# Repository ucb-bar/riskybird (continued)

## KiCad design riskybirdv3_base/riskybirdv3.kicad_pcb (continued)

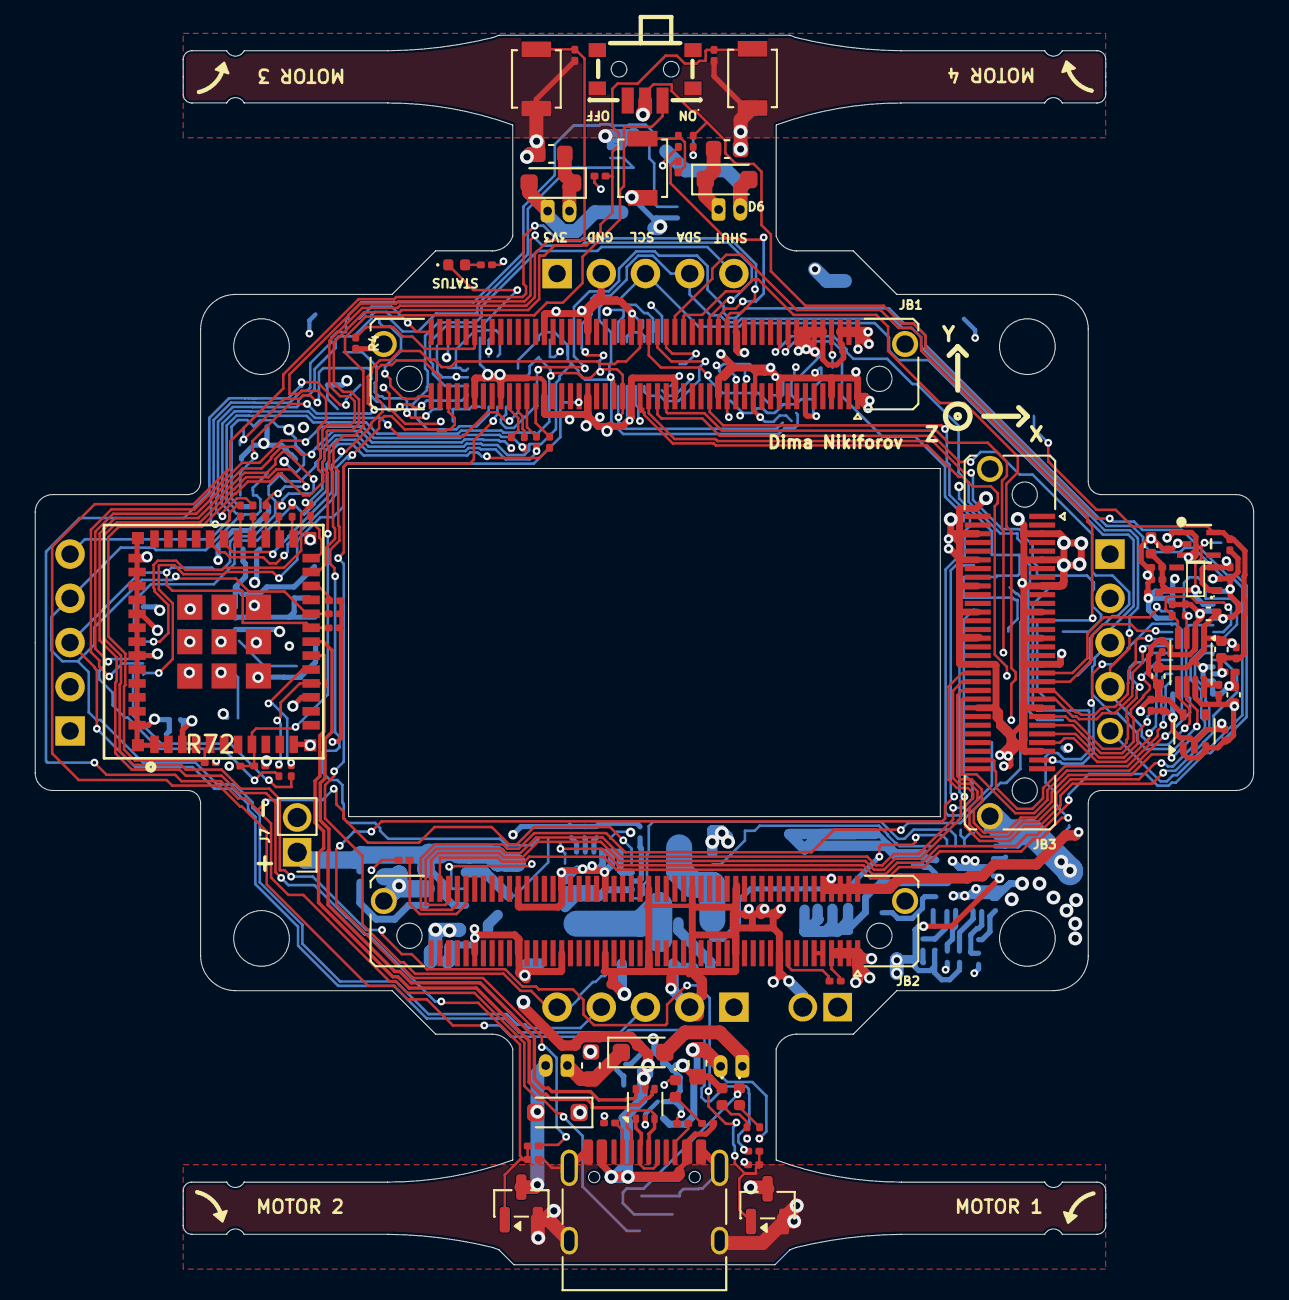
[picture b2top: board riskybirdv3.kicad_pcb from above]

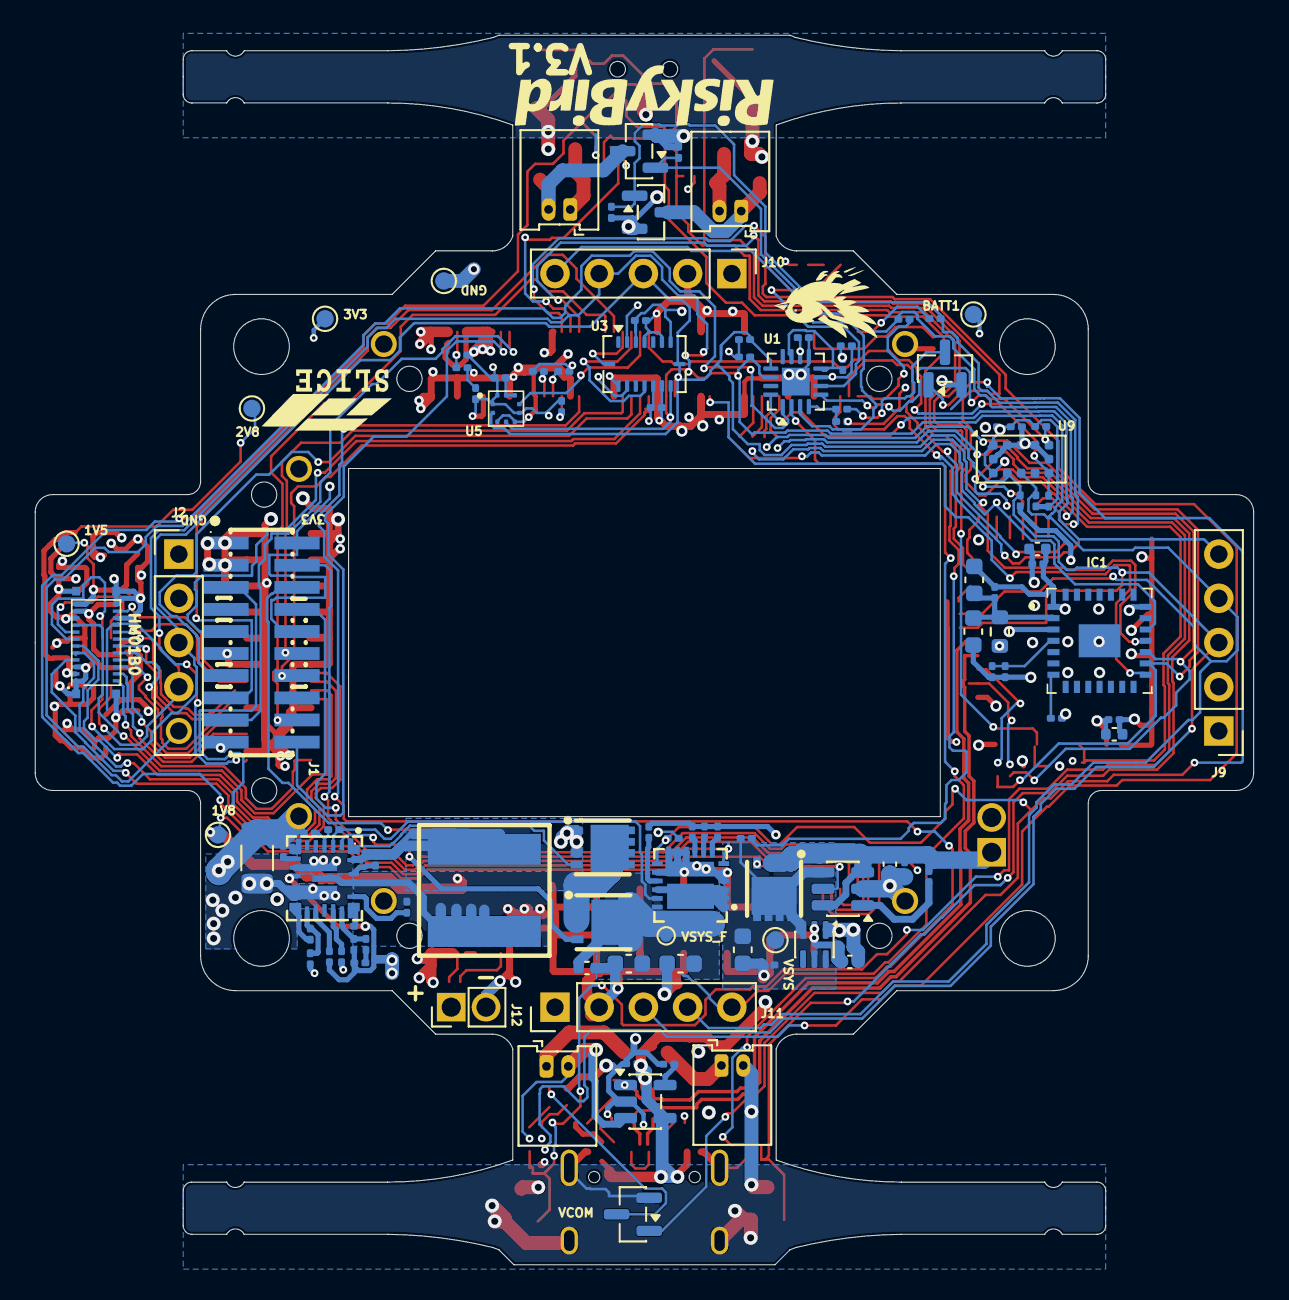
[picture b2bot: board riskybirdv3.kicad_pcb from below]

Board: 4 copper layers, 70.0 x 70.6 mm, 199 parts (108 on the bottom side), 138 nets.

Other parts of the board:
G1: LOGO

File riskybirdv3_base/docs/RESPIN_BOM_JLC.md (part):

# RESPIN — JLCPCB Assembly BOM audit + substitution list

**Project:** riskybird v3 base board (`riskybirdv3_base/riskybirdv3.kicad_sch`)
**Goal:** a BOM JLC can use to **directly SMT-assemble** the respin board — every part verified against JLC's *assembly parts library* (Basic / Preferred Extended / Extended), not merely "listed on LCSC."
**Status:** Audit only — **no `.kicad_*` edits, nothing committed.** Companion to `RESPIN_POWER_RAIL.md`, `RESPIN_POWER_U2.md`, `RESPIN_POWER_BROWNOUT.md`, `RESPIN_CHECKLIST.md`, `OFF-BOM_PARTS_ORDER.md`.
**Date:** 2026-08-16

---

## 0. Method, data source, reliability

- **BOM extracted** from the live schematic with `kicad-cli sch export bom` (grouped by Value+Footprint). The schematic carries LCSC C-numbers in a property named **`LCSC Part`** (126 of 419 symbols populated) — the bennymeg *Fabrication Toolkit* plugin (this project's `fabrication-toolkit-options.json`) reads that field, so the flow is compatible. There is **no** bare `LCSC` property; parts without a `LCSC Part` value are the "no-LCSC" gaps below.
- **JLC assembly status** (in-catalog? class? stock? price?) queried from **`jlcsearch.tscircuit.com/api`**, which is a hosted mirror of the **community `jlcparts` SQLite database** (github.com/yaqwsx/jlcparts) — i.e. JLC's *assembly* catalog, exactly the source the brief recommended. The GitHub-Pages raw DB path (`yaqwsx.github.io/jlcparts/data/cache.json`) now 404s, so the tscircuit mirror was used instead. Fields returned per part: `is_basic`, `is_preferred`, `stock`, `price`, `package`, `mfr`, `description`.
- **Reliability:**
  - **In-catalog (assemblable y/n) — HIGH.** A part returned by the mirror is in the jlcparts assembly DB; a part with **0 results is not in the assembly catalog** (may be LCSC-order-only or discontinued). This is how the BMP390 and the eFuse gaps were found.
  - **Class (Basic/Preferred/Extended) — HIGH.** Stable field.
  - **Stock — MEDIUM (point-in-time snapshot; some noise).** The jlcparts DB is refreshed periodically, so absolute stock is approximate. Observed noise: one jellybean 4.7 kΩ 0201 briefly read "9" then "1.3 M" on re-query. **Treat all stock counts below as order-time-verify**, especially the low ones. Re-check any part at `jlcpcb.com/partdetail/<C#>` before the order.
  - **Not verifiable from this source:** exact assembly-line placement rules for odd packages, and JLC's per-order "economic vs standard" surcharge for Extended parts (every non-Basic part on an SMT order incurs a per-unique-part feeder fee — noted where it matters).

**Headline:** The board is **NOT yet fully JLC-assemblable as drawn.** The silicon is nearly all in the catalog, but **~26 line-items have no `LCSC Part` field** (JLC would skip them), **1 part is genuinely not in the assembly catalog (U5 BMP390)**, and the **3 new power-rail parts** need their C-numbers pinned (buck-boost OK, eFuse + inductor need the corrected C#s below). All gaps have a concrete JLC-assemblable fix listed. Count: **1 not-assemblable, ~26 no-LCSC-field, ~6 low-stock watch items.**

## 0a. Applied changes (2026-08-16) — U5 swap + IC1 DNP/LCSC

Two fixes were **applied to `riskybirdv3.kicad_sch` AND `riskybirdv3.kicad_pcb`** (backups `*.bak_20260816_142627`; **not committed**; validated: BOM re-export ✓, ERC unchanged at 182 before/after, PCB loads via pcbnew, IC1 now present in the `--exclude-dnp` position file):

- **U5 BMP390 → BMP388** (the not-assemblable part). Value `BMP390→BMP388`, MPN `BMP390L→BMP388`, `LCSC Part C2684802→C779278`, in both schematic instance and PCB footprint fields. **Footprint land pattern `riskybird:BMP390` kept** (BMP388 = same LGA-10 2×2 package/pinout). *Note:* the `lib_id`/footprint name still reads "BMP390" (cosmetic; the BOM Value/MPN/LCSC are now BMP388/C779278). Firmware baro driver must cover BMP388.
- **IC1 PMW3901 un-DNP'd + LCSC added.** Cleared `(attr smd dnp)` → `(attr smd)` on the PCB footprint (the actual "BOM-yes/CPL-no" desync cause — the schematic symbol was already `dnp=no`), and added `LCSC Part = C43496881` to both the schematic symbol and PCB footprint. IC1 now exports into the position/CPL file.

**Still a GUI follow-up (recommended):** open KiCAD and run **Update PCB from Schematic (F8)** once to confirm sch↔pcb parity (fields were edited on both sides to match, so no geometry change is expected). And when the *other* §2 no-LCSC parts get their C#s, pin them in the schematic and re-run F8.

**B2B connectors actually ordered (from the real order BOM `production/riskybirdv3-bom.csv`, 2026-07-26):** the **LSHM-04.0 / 8.00 mm stack** — JB1+JB2 = `LSHM-150-04.0-L-DV-A-S-K-TR` (**C5367357**, qty 2), JB3 = `LSHM-130-04.0-L-DV-A-S-K-TR` (**C3645597**, qty 1). **Not** the 03.0/7.00 mm option. So the current schematic already matches what was ordered; the 03.0-vs-04.0 "contradiction" resolves to **04.0** for the respin (and 04.0 has more JB1/JB2 stock than 03.0 — 11 vs 1).

---

## 1. Full BOM — JLC assembly status

Legend for **STATUS**: **OK** = has C#, in catalog, adequate stock · **NO-LCSC** = in catalog but no `LCSC Part` field in schematic (JLC will skip until assigned) · **NOT-ASM** = not in JLC assembly catalog · **LOW-STK** = assemblable but thin stock (order-time verify) · **THT** = through-hole (JLC THT-assembly upcharge, else hand-solder) · **N/A** = not a placed part.

Class = Basic / Pref (Preferred Extended) / Ext (Extended). Stock/price are the 2026-08-16 snapshot.

| Ref(s) | Value | Footprint | MPN | LCSC (in sch) | Class | Stock | Price | STATUS |
|---|---|---|---|---|---|---|---|---|
| 1V5,1V8,2V8,3V3,BATT1,TP1,TP2 | TestPoint | Pad_D1.0mm | — | — | — | — | — | **N/A** (bare pads, not placed) |
| C1 | 4.7µ | 0201 | GRM035R60J475ME15D | C335103 | Ext | 684k | $0.20 | OK |
| C2,C3,C40,C41 | 47µF | 0603 | — | — | — | — | — | **NO-LCSC** → C140782 |
| C4,C5,C6,C7,C10,C13,C15,C38 | 100nF | 0201 | GRM033R60J104KE19D | C76928 | Ext | 2.56M | $0.001 | OK |
| C8,C42,C59,C66 | 1µF | 0201 | CL03A105MQ3CSNH | C53067 | Ext | 43k | $0.004 | OK |
| C9,C39 | 4.7µF | 0201 | GRM035R60J475ME15D | C335103 | Ext | 684k | $0.20 | OK |
| C11,C12 | 22µF | 0603 | — | — | — | — | — | **NO-LCSC** → C59461 (Basic) |
| C14 | 10µF | 0402 | — | — | — | — | — | **NO-LCSC** → C15525 (Basic) |
| C16,C17 | 100n | 0201 | GRM033R60J104KE19D | C76928 | Ext | 2.56M | $0.001 | OK |
| C37,C43,C44,C45,C50,C51,C54,C56–C58,C60,C61,C77 | 0.1µ | 0201 | GRM033R60J104KE19D | C76928 | Ext | 2.56M | $0.001 | OK |
| C46,C47,C48,C49,C62,C67,C73,C74,C75 | 10µ | 0402 | — | — | — | — | — | **NO-LCSC** → C15525 (Basic) |
| C52,C53,C55,C68,C69,C70 | 1µ | 0201 | CL03A105MQ3CSNH | C53067 | Ext | 43k | $0.004 | OK |
| C63 | 150µ | 1206 | — | — | — | — | — | **NO-LCSC** → C528968 |
| C64 | 470p | 0201 | GRM033R71H471KA12D | C161493 | Ext | 12k | $0.003 | OK |
| C65 | 4.7µ | 0402 | — | — | — | — | — | **NO-LCSC** → C23733 (Basic) |
| C71,C72 | 0.1µ | 0402 | — | — | — | — | — | **NO-LCSC** → C1525 (Basic) |
| D1,D4 | LED | 0402 | — | — | — | — | — | **NO-LCSC** → C965793 (grn) / C20613596 (wht) — pick color |
| D2,D3,D5,D6 | BAT54JFILM | SOD-323 | — | — | — | — | — | **NO-LCSC** → C86299 |
| D7 | LED_RED | 0402 | — | — | — | — | — | **NO-LCSC** → C25503345 |
| HM01B0 | camera recept. | 5055502420 | 505550-2420 | C3642262 | Ext | 5112 | $0.37 | OK (mates HM01B0 module plug) |
| IC1 | PMW3901MB-TXQT | COB/LGA-28 | — | **C43496881** ✅ | Ext | 596 | $4.96 | **FIXED 2026-08-16** — LCSC added + PCB `dnp` cleared (§0a) |
| J1 | FTSH-110-01-L-DV-K-TR | 2×10 1.27mm | FTSH-110-01-L-DV-K-TR | C20728453 | Ext | **31** | $2.85 | **LOW-STK** (debug hdr) |
| J2,J9,J10,J11 | Conn_01x05 | 1×5 2.54mm hdr | — | — | Ext | 251k | $0.03 | **NO-LCSC + THT** → C492404 |
| J3,J4,J5,J6 | Conn_01x02 | Molex PicoBlade 53048-0210 | 53048-0210 | C505099 | Ext | 30.8k | $0.14 | OK as drawn — **respin: upsize** (1A/contact, see §5) |
| J8 | USB-C recept. | TYPE-C-31-M-12 | TYPE-C-31-M-12 | C165948 | Ext | 336k | $0.16 | OK |
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
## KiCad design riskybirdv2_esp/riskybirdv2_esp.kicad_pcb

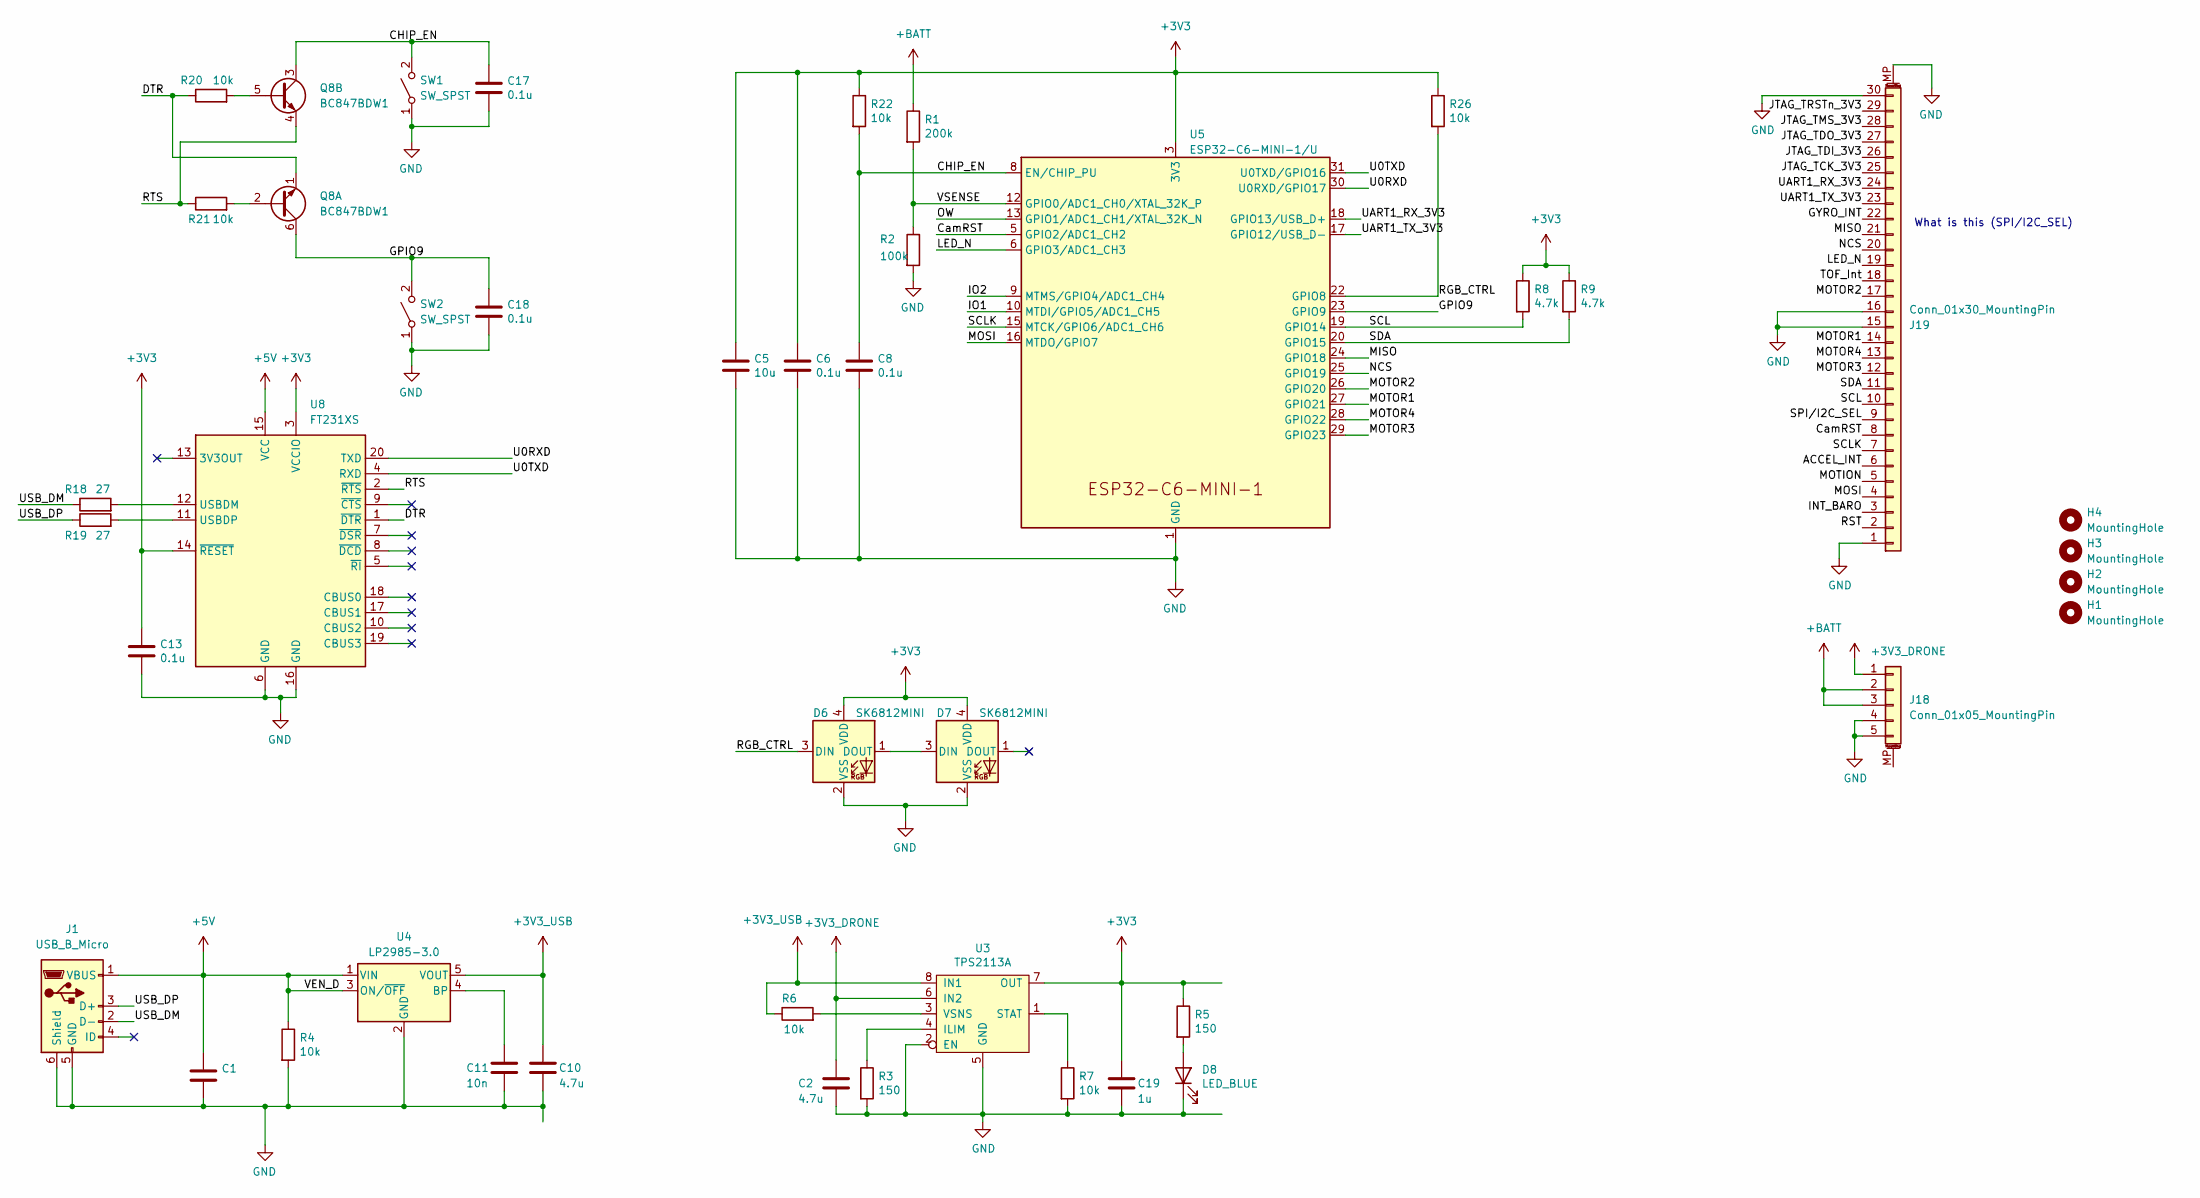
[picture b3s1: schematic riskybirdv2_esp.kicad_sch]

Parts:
C1, C2, C10: 4.7u; C_0402_1005Metric
C5: 10u; C_0402_1005Metric
C6, C8, C13, C17, C18: 0.1u; C_0402_1005Metric
C11: 10n; C_0402_1005Metric
C19: 1u; C_0402_1005Metric
D6, D7: SK6812MINI; LED_SK6812MINI_PLCC4_3.5x3.5mm_P1.75mm
D8: LED_BLUE; LED_0805_2012Metric_Pad1.15x1.40mm_HandSolder
H1, H2, H3, H4: MountingHole; MountingHole_2.2mm_M2
J1: USB_B_Micro; USB_Micro-B_Molex_47346-0001
J18: Conn_01x05_MountingPin; JST_ZH_B5B-ZR_1x05_P1.50mm_Vertical
J19: Conn_01x30_MountingPin; Hirose_FH12-30S-0.5SH_1x30-1MP_P0.50mm_Horizontal
Q8: BC847BDW1; SOT-363_SC-70-6
R1: 200k; R_0402_1005Metric
R2: 100k; R_0402_1005Metric
R3, R5: 150; R_0402_1005Metric
R4, R6, R7, R20, R21, R22, R26: 10k; R_0402_1005Metric
R8, R9: 4.7k; R_0402_1005Metric
R18, R19: 27; R_0402_1005Metric
SW1, SW2: SW_SPST; SW_SPST_B3U-1000P
U3: TPS2113A; TSSOP-8_4.4x3mm_P0.65mm
U4: LP2985-3.0; SOT-23-5
U5: ESP32-C6-MINI-1/U; ESP32-C6-MINI-1
U8: FT231XS; SSOP-20_3.9x8.7mm_P0.635mm

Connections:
+3V3: C5.1, C6.1, C13.1, C19.1, D6.4 (VDD), D7.4 (VDD), R5.1, R8.1, R9.1, R22.1, R26.1, U3.7 (OUT), U5.3 (3V3), U8.3 (VCCIO), U8.14 (~RESET)
+3V3_DRONE: C2.1, J18.1, U3.6 (IN2)
+3V3_USB: C10.1, R6.1, U3.8 (IN1), U4.5 (VOUT)
+5V: C1.1, J1.1 (VBUS), R4.1, U4.1 (VIN), U4.3 (ON/~OFF), U8.15 (VCC)
+BATT: J18.2, J18.3, R1.1
/ACCEL_INT: J19.6
/CHIP_EN: C8.1, C17.1, Q8.3 (C2), R22.2, SW1.2 (B), U5.8 (EN/CHIP_PU)
/CamRST: J19.8, U5.5 (GPIO2/ADC1_CH2)
/DTR: Q8.1 (E1), R20.1, U8.1 (~DTR)
/GPIO9: C18.1, Q8.6 (C1), SW2.2 (B), U5.23 (GPIO9)
/GYRO_INT: J19.22
/INT_BARO: J19.3
/IO1: U5.10 (MTDI/GPIO5/ADC1_CH5)
/IO2: U5.9 (MTMS/GPIO4/ADC1_CH4)
/JTAG_TCK_3V3: J19.25
/JTAG_TDI_3V3: J19.26
/JTAG_TDO_3V3: J19.27
/JTAG_TMS_3V3: J19.28
/JTAG_TRSTn_3V3: J19.29
/LED_N: J19.19, U5.6 (GPIO3/ADC1_CH3)
/MISO: J19.21, U5.24 (GPIO18)
/MOSI: J19.4, U5.16 (MTDO/GPIO7)
/MOTION: J19.5
/MOTOR1: J19.14, U5.27 (GPIO21)
/MOTOR2: J19.17, U5.26 (GPIO20)
/MOTOR3: J19.12, U5.29 (GPIO23)
/MOTOR4: J19.13, U5.28 (GPIO22)
/NCS: J19.20, U5.25 (GPIO19)
/OW: U5.13 (GPIO1/ADC1_CH1/XTAL_32K_N)
/RGB_CTRL: D6.3 (DIN), R26.2, U5.22 (GPIO8)
/RST: J19.2
/RTS: Q8.4 (E2), R21.1, U8.2 (~RTS)
/SCL: J19.10, R8.2, U5.19 (GPIO14)
/SCLK: J19.7, U5.15 (MTCK/GPIO6/ADC1_CH6)
/SDA: J19.11, R9.2, U5.20 (GPIO15)
/SPI/I2C_SEL: J19.9
/TOF_Int: J19.18
/U0RXD: U5.30 (U0RXD/GPIO17), U8.20 (TXD)
/U0TXD: U5.31 (U0TXD/GPIO16), U8.4 (RXD)
/UART1_RX_3V3: J19.24, U5.18 (GPIO13/USB_D+)
/UART1_TX_3V3: J19.23, U5.17 (GPIO12/USB_D-)
/USB_DM: J1.2 (D-), R18.1
/USB_DP: J1.3 (D+), R19.1
/VSENSE: R1.2, R2.1, U5.12 (GPIO0/ADC1_CH0/XTAL_32K_P)
GND: C1.2, C2.2, C5.2, C6.2, C8.2, C10.2, C11.2, C13.2, C17.2, C18.2, C19.2, D6.2 (VSS), D7.2 (VSS), D8.1 (K), J1.5 (GND), J1.6 (Shield), J18.4, J18.5, J19.1, J19.15, J19.16, J19.30, J19.MP (MountPin), R2.2, R3.2, R4.2, R7.2, SW1.1 (A), SW2.1 (A), U3.2 (EN), U3.5 (GND), U4.2 (GND), U5.1 (GND), U5.2 (GND), U5.11 (GND), U5.14 (GND), U5.36 (GND), U5.37 (GND), U5.38 (GND), U5.39 (GND), U5.40 (GND), U5.41 (GND), U5.42 (GND), U5.43 (GND), U5.44 (GND), U5.45 (GND), U5.46 (GND), U5.47 (GND), U5.48 (GND), U5.49 (GND), U5.50 (GND), U5.51 (GND), U5.52 (GND), U5.53 (GND), U8.6 (GND), U8.16 (GND)
unnamed: D6.1 (DOUT), D7.3 (DIN)
unnamed: D8.2 (A), R5.2
unnamed: Q8.2 (B1), R21.2
unnamed: Q8.5 (B2), R20.2
unnamed: R3.1, U3.4 (ILIM)
unnamed: R7.1, U3.1 (STAT)
unnamed: R6.2, U3.3 (VSNS)
unnamed: C11.1, U4.4 (BP)
unnamed: R18.2, U8.12 (USBDM)
unnamed: R19.2, U8.11 (USBDP)

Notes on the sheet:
What is this (SPI/I2C_SEL)

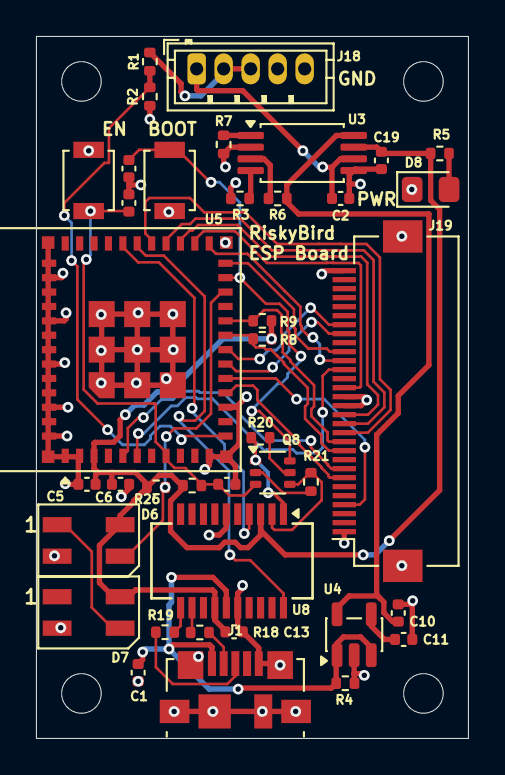
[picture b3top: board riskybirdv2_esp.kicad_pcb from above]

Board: 2 copper layers, 24.0 x 39.0 mm, 47 parts (0 on the bottom side), 40 nets.

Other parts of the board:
H1#2, H2#2, H3#2, H4#2: MountingHole; MountingHole_2.2mm_M2

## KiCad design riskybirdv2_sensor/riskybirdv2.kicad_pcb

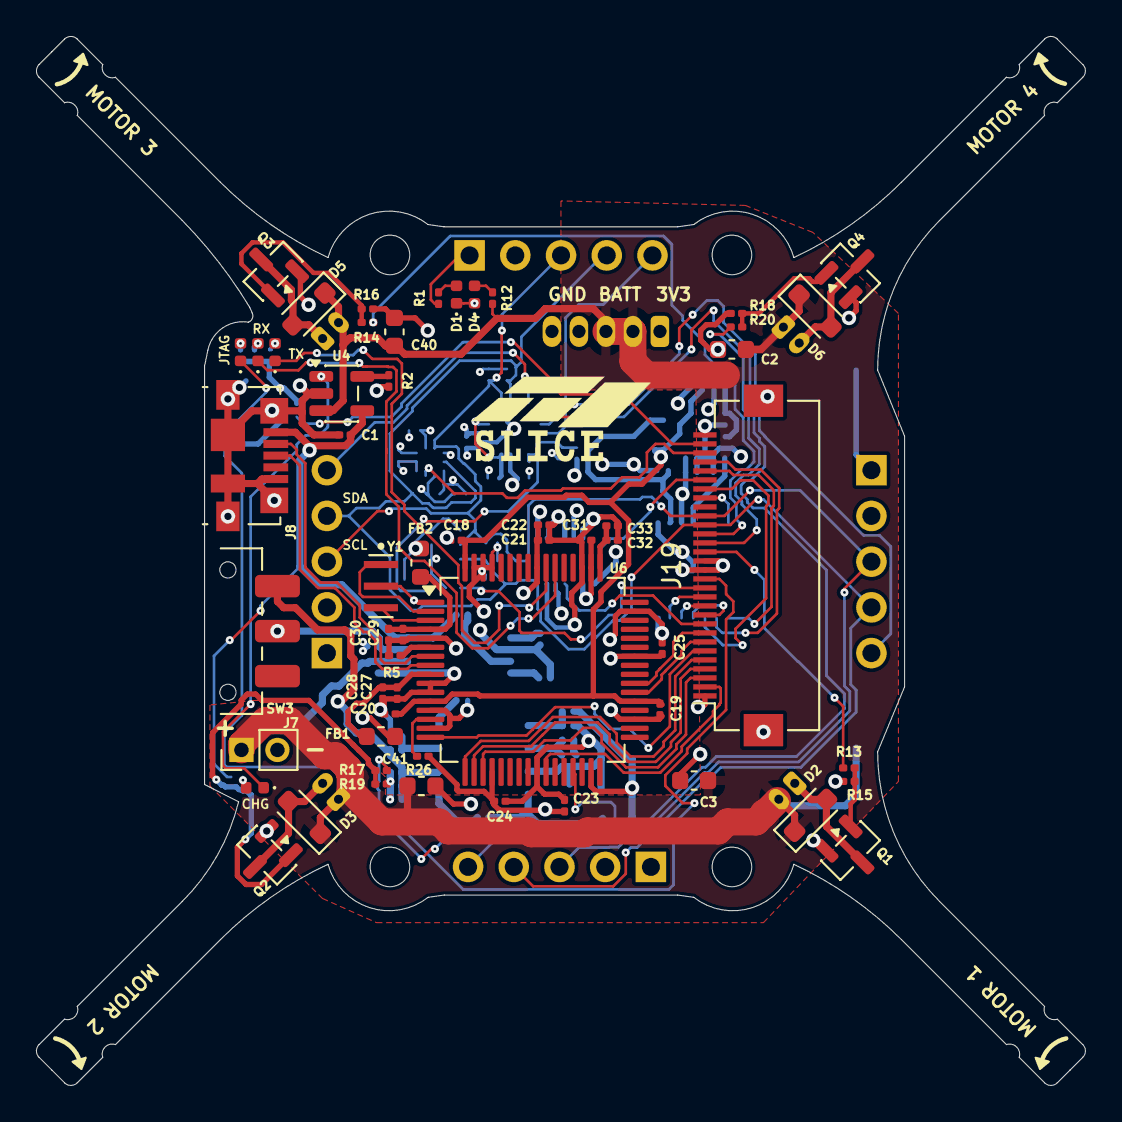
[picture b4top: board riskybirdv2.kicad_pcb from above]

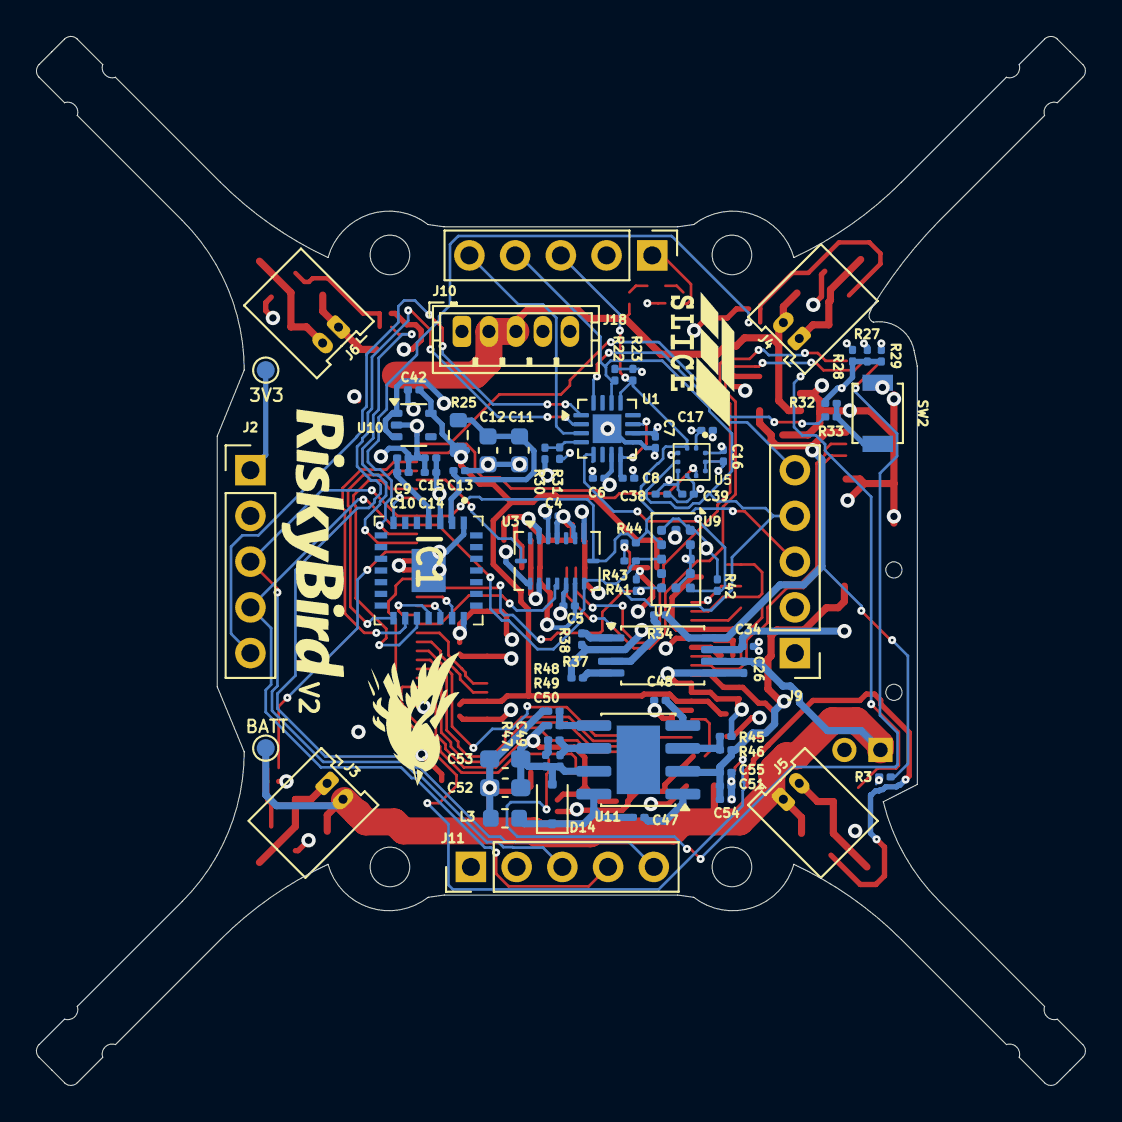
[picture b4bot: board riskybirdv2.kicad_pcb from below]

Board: 4 copper layers, 58.3 x 58.3 mm, 134 parts (73 on the bottom side), 80 nets.

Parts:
C1, C26: 4.7u; C_0201_0603Metric
C2, C3, C40, C41: 47uF; C_0603_1608Metric
C4, C5, C6, C7, C10, C13, C15, C18, C19, C20, C21, C22, C24, C25, C27, C29, C31, C33, C38: 100nF; C_0201_0603Metric
C8, C42: 1uF; C_0201_0603Metric
C9, C28, C30, C39, C51, C55: 4.7uF; C_0201_0603Metric
C11, C12: 22uF; C_0603_1608Metric
C14, C23: 10uF; C_0201_0603Metric
C16, C17: 100n; C_0201_0603Metric
C32: 3.3uF; C_0201_0603Metric
C34: 1u; C_0201_0603Metric
C47: 0.1uF; C_0201_0603Metric
C48, C54: 0.01uF; C_0201_0603Metric
C49: 1000pF; C_0201_0603Metric
C50: 47pF; C_0201_0603Metric
C52, C53: 47uF; C_0603_1608Metric_Pad1.08x0.95mm_HandSolder
D1, D4, D10, D11, D12: LED; LED_0402_1005Metric
D2, D3, D5, D6: BAT54JFILM; D_SOD-323_HandSoldering
D7: LED_RED; LED_0402_1005Metric
D14: BAT54J; D_SOD-323F
FB1, FB2: 600R@100MHz/0.5A; L_0603_1608Metric
FID1: DroneFrame; riskybird_frame
H1, H2, H3, H4: MountingHole; MountingHole_2.2mm_M2
IC1: PMW3901MB-TXQT; PMW3901MBTXQT
J2, J9, J10, J11: Conn_01x05; PinHeader_1x05_P2.54mm_Vertical
J3, J4, J5, J6: Conn_01x02; Molex_PicoBlade_53048-0210_1x02_P1.25mm_Horizontal
J7: Conn_01x02; PinHeader_1x02_P2.00mm_Vertical
J8: USB_B_Micro; USB_Micro-B_Molex_47346-0001
J18: Conn_01x05_MountingPin; JST_ZH_B5B-ZR_1x05_P1.50mm_Vertical
J19: Conn_01x30_MountingPin; Hirose_FH12-30S-0.5SH_1x30-1MP_P0.50mm_Horizontal
L3: 6.8uH; L_0603_1608Metric
Q1, Q2, Q3, Q4: SI2302; SOT-23
R1, R3, R12, R27, R28, R29, R37: 150; R_0201_0603Metric
R2: 2k; R_0201_0603Metric
R5: 12k; R_0201_0603Metric
R13, R14, R17, R18: 47R; R_0201_0603Metric
R15, R16, R19, R20, R34, R38, R41, R42: 10k; R_0201_0603Metric
R22, R23, R43, R44: 4.7K; R_0201_0603Metric
R25: 3; R_0603_1608Metric
R26: 1k; R_0201_0603Metric
R30: 200K; R_0201_0603Metric
R31: 100K; R_0201_0603Metric
R32: 10K; R_0201_0603Metric
R33: 100; R_0201_0603Metric
R45: 68.1k; R_0201_0603Metric
R46: 332k; R_0201_0603Metric
R47: 29.4k; R_0201_0603Metric
R48: 10.2k; R_0201_0603Metric
R49: 3.24k; R_0201_0603Metric
SW2: SW_SPST; SW_SPST_B3U-1000P
SW3: SW_SPST; SW_SPDT_CK_JS102011SAQN
TP1, TP6: TestPoint; TestPoint_Pad_D1.0mm
U1: ADS7128IRTER; WQFN-16-1EP_3x3mm_P0.5mm_EP1.6x1.6mm
U3: BMI088; Bosch_LGA-16_4.5x3mm_P0.5mm_LayoutBorder7x1y_ClockwisePinNu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
U4: MCP73831-2-OT; SOT-23-5
U5: BMP390
U6: FT2232HL-REEL; LQFP-64_10x10mm_P0.5mm
U7: TPS2113A; TSSOP-8_4.4x3mm_P0.65mm
U9: VL53L1CXV0FY1; ST_VL53L1x
U10: TLV70018DCKR; SOT-353_SC-70-5
U11: TPS54331D; SOIC-8-1EP_3.9x4.9mm_P1.27mm_EP2.41x3.81mm
Y1: f; OSC_CSTNE12M0G550000R0

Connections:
+1V8: C18.1, C19.1, C20.1, C42.1, R25.2, U6.12 (VCORE), U6.37 (VCORE), U6.64 (VCORE), U10.5 (OUT)
+3V3: C4.1, C5.1, C6.1, C7.1, C14.1, C15.1, C16.1, C17.1, C21.1, C22.1, C23.1, C24.1, C25.1, C31.1, C38.1, C39.1, C52.2, C53.2, FB1.2, FB2.2, IC1.3 (VDDIO), J2.1, J9.1, J10.1, J11.1, J18.1, L3.2, R1.1, R22.1, R23.1, R26.1, R27.1, R28.1, R29.1, R30.1, R32.1, R41.1, R42.1, R43.1, R44.1, R48.1, TP6.1, U1.7 (AVDD), U1.10 (DVDD), U3.3 (VDD), U3.7 (PS), U3.11 (VDDIO), U3.14 (CSB1), U5.1 (VDDIO), U5.6 (CSB), U5.10 (VDD), U6.20 (VCCIO), U6.31 (VCCIO), U6.42 (VCCIO), U6.50 (VREGIN), U6.56 (VCCIO), U6.61 (EEDATA), U6.62 (EECLK), U6.63 (EECS), U9.1 (AVDDVCSEL), U9.11 (AVDD), U10.1 (IN), U10.3 (EN)
+5V: C1.1, J8.1 (VBUS), R3.1, R34.1, U4.4 (VDD), U7.8 (IN1)
+BATT: C2.1, C3.1, C26.1, C40.1, C41.1, D2.1 (K), D3.1 (K), D5.1 (K), D6.1 (K), J3.2, J4.2, J5.1, J6.1, J7.1, J18.2, J18.3, R12.1, TP1.1, U4.3 (VBAT), U7.6 (IN2)
/ACCEL_INT: J19.25, U3.16 (INT1)
/CamRST: IC1.7 (NRESET), J19.23
/DECAP: C8.1, U1.8 (DECAP), U1.11 (ADDR)
/FTDI_OSCI: U6.2 (OSCI), Y1.1
/FTDI_OSCO: U6.3 (OSCO), Y1.3
/GPIO1: J9.5, U1.16 (AIN1/GPIO1)
/GPIO2: J2.5, U1.1 (AIN2/GPIO2)
/GPIO3: J11.5, U1.2 (AIN3/GPIO3)
/GPIO4: J10.5, U1.3 (AIN4/GPIO4)
/GPIO5: R30.2, R31.1, U1.4 (AIN5/GPIO5)
/GPIO6: R42.2, U1.5 (AIN6/GPIO6), U9.5 (XSHUT)
/GYRO_INT: J19.9, U3.12 (INT3)
/INT_BARO: J19.28, U5.7 (INT)
/JTAG_LED: D12.1 (K), U6.29 (ACBUS3)
/JTAG_TCK_3V3: J19.6, U6.16 (ADBUS0)
/JTAG_TDI_3V3: J19.5, U6.17 (ADBUS1)
/JTAG_TDO_3V3: J19.4, U6.18 (ADBUS2)
/JTAG_TMS_3V3: J19.3, U6.19 (ADBUS3)
/JTAG_TRSTn_3V3: J19.2, U6.26 (ACBUS0)
/LED_N: IC1.20 (LED_N), J19.12
/MISO: IC1.18 (MISO), J19.10
/MOSI: IC1.16 (MOSI), J19.27
/MOTION: IC1.15 (MOTION), J19.26
/MOTOR1: J19.17, R13.1
/MOTOR2: J19.14, R17.1
/MOTOR3: J19.19, R14.1
/MOTOR4: J19.18, R18.1
/NCS: IC1.19 (NCS), J19.11
/RST: J19.29, R33.2
/RX_LED: D10.1 (K), U6.54 (BCBUS3)
/SCL: J2.3, J9.3, J10.3, J11.3, J19.21, R23.2, R44.2, U1.13 (SCL), U3.8 (SCL/SCK), U5.2 (SCL/SCK), U9.10 (SCL)
/SCLK: IC1.17 (SCLK), J19.24
/SDA: J2.4, J9.4, J10.4, J11.4, J19.20, R22.2, R43.2, U1.14 (SDA), U3.9 (SDA/SDI), U5.4 (SDA/SDI), U9.9 (SDA)
/TOF_Int: J19.13, R41.2, U9.7 (GPIO1)
/TX_LED: D11.1 (K), U6.55 (BCBUS4)
/UART0_RX_3V3: J19.7, U6.38 (BDBUS0)
/UART0_TX_3V3: J19.8, U6.39 (BDBUS1)
/USB_DN: J8.2 (D-), U6.7 (DM)
/USB_DP: J8.3 (D+), U6.8 (DP)
/VSENSE: R48.2, R49.1, U11.5 (VSENSE)
GND: C1.2, C2.2, C3.2, C4.2, C5.2, C6.2, C7.2, C8.2, C9.2, C10.2, C11.2, C12.2, C13.2, C14.2, C15.2, C16.2, C17.2, C18.2, C19.2, C20.2, C21.2, C22.2, C23.2, C24.2, C25.2, C26.2, C27.2, C28.2, C29.2, C30.2, C31.2, C32.2, C33.2, C34.2, C38.2, C39.2, C40.2, C41.2, C42.2, C48.1, C49.1, C51.1, C52.1, C53.1, C54.1, C55.1, D1.1 (K), D4.1 (K), D14.2 (A), IC1.1 (GND_1), IC1.21 (GND_2), IC1.29 (EP), J2.2, J7.2, J8.5 (GND), J8.6 (Shield), J9.2, J10.2, J11.2, J18.4, J18.5, J19.1, J19.15, J19.16, J19.30, J19.MP (MountPin), Q1.2 (S), Q2.2 (S), Q3.2 (S), Q4.2 (S), R2.2, R5.2, R15.2, R16.2, R19.2, R20.2, R31.2, R37.2, R38.2, R45.2, R47.2, R49.2, SW2.1 (A), U1.9 (GND), U1.17 (GND), U3.2 (NC), U3.4 (GNDA), U3.6 (GNDIO), U3.10 (SDO2), U3.15 (SDO1), U4.2 (VSS), U5.3 (VSS), U5.5 (ADR/SDO), U5.8 (VSS), U5.9 (VSS), U6.1 (GND), U6.5 (GND), U6.10 (AGND), U6.11 (GND), U6.13 (TEST), U6.15 (GND), U6.25 (GND), U6.35 (GND), U6.47 (GND), U6.51 (GND), U7.2 (EN), U7.5 (GND), U9.2 (AVSSVCSEL), U9.3 (GND), U9.4 (GND), U9.6 (GND), U9.12 (GND), U10.2 (GND), U11.7 (GND), Y1.2
unnamed: C50.1, R47.1
unnamed: D1.2 (A), R1.2
unnamed: D2.2 (A), J3.1, Q1.3 (D)
unnamed: D3.2 (A), J5.2, Q2.3 (D)
unnamed: D4.2 (A), R12.2
unnamed: D5.2 (A), J4.1, Q3.3 (D)
unnamed: D6.2 (A), J6.2, Q4.3 (D)
unnamed: D7.2 (A), R3.2
unnamed: D7.1 (K), U4.1 (STAT)
unnamed: D10.2 (A), R27.2
unnamed: D11.2 (A), R28.2
unnamed: D12.2 (A), R29.2
unnamed: C47.2, D14.1 (K), L3.1, U11.8 (PH)
unnamed: C11.1, C12.1, C13.1, IC1.2 (VDD), R25.1
unnamed: C9.1, C10.1, IC1.4 (VREG)
unnamed: Q1.1 (G), R13.2, R15.1
unnamed: Q2.1 (G), R17.2, R19.1
unnamed: Q3.1 (G), R14.2, R16.1
unnamed: Q4.1 (G), R18.2, R20.1
unnamed: R32.2, R33.1, SW2.2 (B)
unnamed: C34.1, SW3.2 (B), U7.7 (OUT)
unnamed: R2.1, U4.5 (PROG)
unnamed: R5.1, U6.6 (REF)
unnamed: R26.2, U6.14 (RESET)
unnamed: C29.1, C30.1, FB2.1, U6.4 (VPHY)
unnamed: C27.1, C28.1, FB1.1, U6.9 (VPLL)
unnamed: C32.1, C33.1, U6.49 (VREGOUT)
unnamed: R37.1, U7.4 (ILIM)
unnamed: R38.1, U7.1 (STAT)
unnamed: R34.2, U7.3 (VSNS)
unnamed: C47.1, U11.1 (BOOT)
unnamed: C49.2, C50.2, U11.6 (COMP)
unnamed: R45.1, R46.2, U11.3 (EN)
unnamed: C48.2, U11.4 (SS)
VCOM: C51.2, C54.2, C55.2, R46.1, SW3.1 (A), U11.2 (VIN)

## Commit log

2023-08-12 Rename Unit1: DNN for Embedded System.md to Unit1 DNN for Embedded System.md
2023-08-12 Rename Unit2: Arduino Basics.md to Unit2 Arduino Basics.md
2023-08-12 Rename Unit3: Running ML on Arduino.md to Unit3 Running ML on Arduino.md
2023-08-12 Rename Unit4a: Sensing and Perception on Arduino.md to Unit4a Sensing and Perception on Arduino.md
2023-08-12 Rename Unit4b: Control on Arduino.md to Unit4b Control on Arduino.md
2023-08-12 Rename Unit5: Flying the RiskyBird.md to Unit5 Flying the RiskyBird.md
2024-02-16 Update linkedin addresses
